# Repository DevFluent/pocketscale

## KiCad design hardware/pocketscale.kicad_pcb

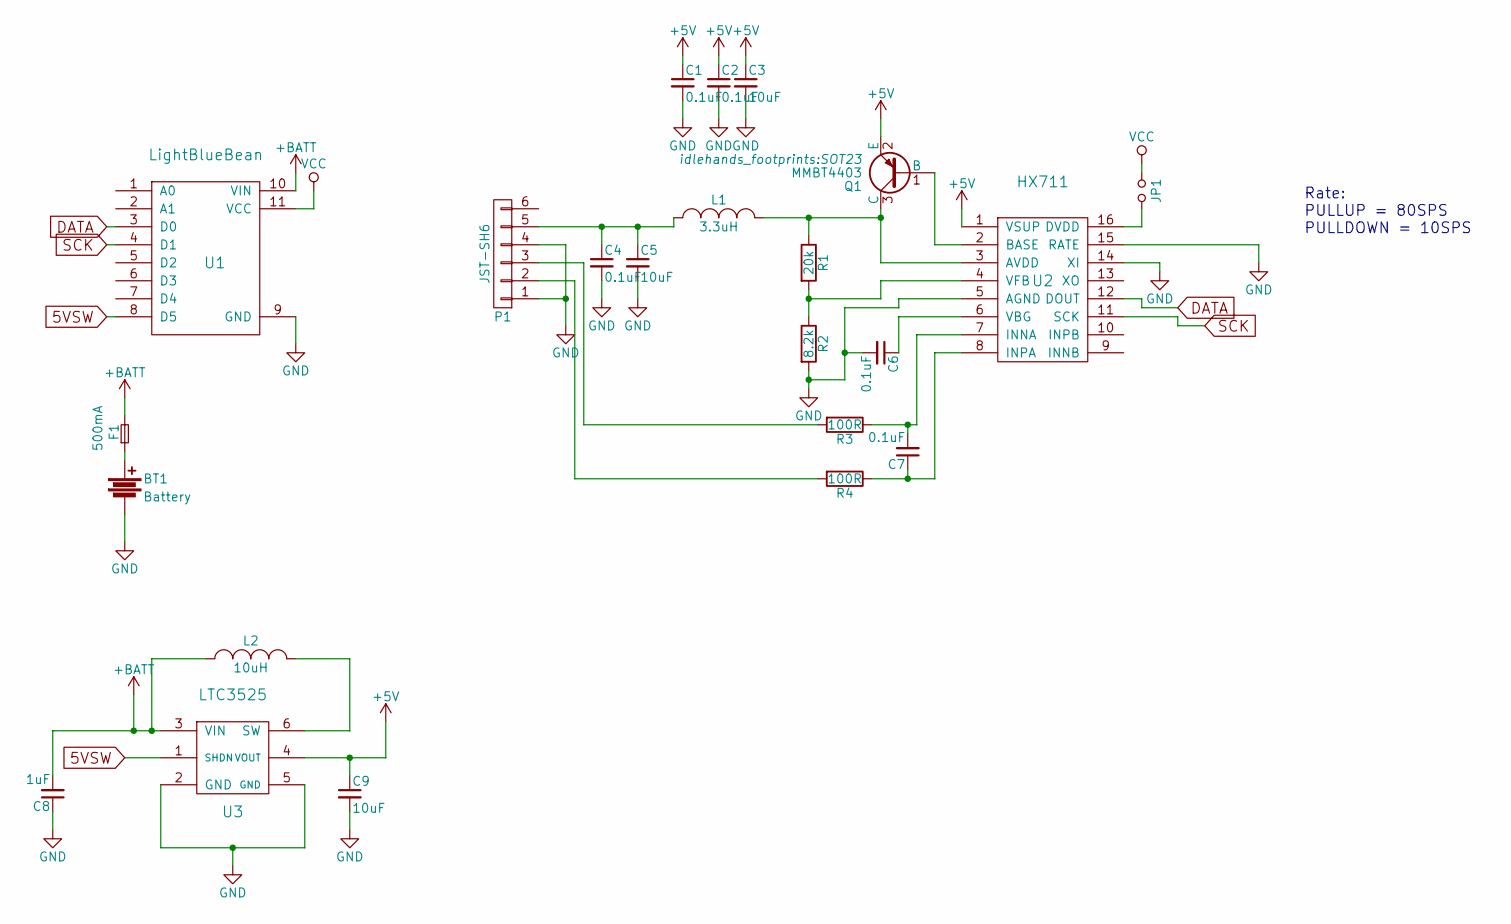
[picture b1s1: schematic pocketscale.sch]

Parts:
BT1: Battery; Pin_Header_Angled_1x02
C1, C2, C4, C6, C7: 0.1uF; C_0402_Hand; Digikey Part No. 490-6328-1-ND
C3, C5, C9: 10uF; c_1206; Digikey Part No. 399-1249-1-ND
C8: 1uF; C_0402_Hand; Digikey Part No. 587-1231-1-ND
F1: 500mA; c_1206
JP1: HX_PWR; Pin_Header_Straight_1x02
L1: 3.3uH; C_SM0603; Digikey Part No. 587-1584-6-ND
L2: 10uH; Inductor_1212; Digikey Part No. 490-6617-1-ND
P1: JST-SH6; Connectors_JST_SM06B-SRSS-TB; Digikey Part No. 455-1806-1-ND
Q1: MMBT4403; SOT23; Digikey Part No. MMBT4403LT3GOSCT-ND
R1: 20k; R_0402_Hand; Digikey Part No. 311-20KJRCT-ND
R2: 8.2k; R_0402_Hand; Digikey Part No. 311-8.2KJRCT-ND
R3, R4: 100R; R_0402_Hand; Digikey Part No. 311-100LRCT-ND
U1: LightBlueBean
U2: HX711; SOP16L
U3: LTC3525; SC70-6; Digikey Part No. LTC3525ESC6-5#TRMPBFCT-ND

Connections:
5VSW: U1.8 (D5), U3.1 (SHDN)
+5V: C1.1, C2.1, C3.1, C9.1, Q1.2 (E), U2.1 (VSUP), U3.4 (VOUT)
+BATT: C8.2, F1.2, L2.1, U1.10 (VIN), U3.3 (VIN)
DATA: U1.3 (D0), U2.12 (DOUT)
GND: BT1.2, C1.2, C2.2, C3.2, C4.2, C5.2, C6.2, C8.1, C9.2, P1.1, P1.4, R2.2, U1.9 (GND), U2.5 (AGND), U2.14 (XI), U2.15 (RATE), U3.2 (GND), U3.5 (GND)
unnamed: BT1.1, F1.1
unnamed: C4.1, C5.1, L1.1, P1.5
unnamed: C6.1, U2.6 (VBG)
unnamed: C7.1, R4.1, U2.8 (INPA)
unnamed: C7.2, R3.1, U2.7 (INNA)
unnamed: JP1.2, U2.16 (DVDD)
unnamed: L1.2, Q1.3 (C), R1.1, U2.3 (AVDD)
unnamed: L2.2, U3.6 (SW)
unnamed: P1.2, R4.2
unnamed: P1.3, R3.2
unnamed: Q1.1 (B), U2.2 (BASE)
unnamed: R1.2, R2.1, U2.4 (VFB)
SCK: U1.4 (D1), U2.11 (SCK)
VCC: JP1.1, U1.11 (VCC)

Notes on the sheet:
Rate: PULLUP = 80SPS PULLDOWN = 10SPS

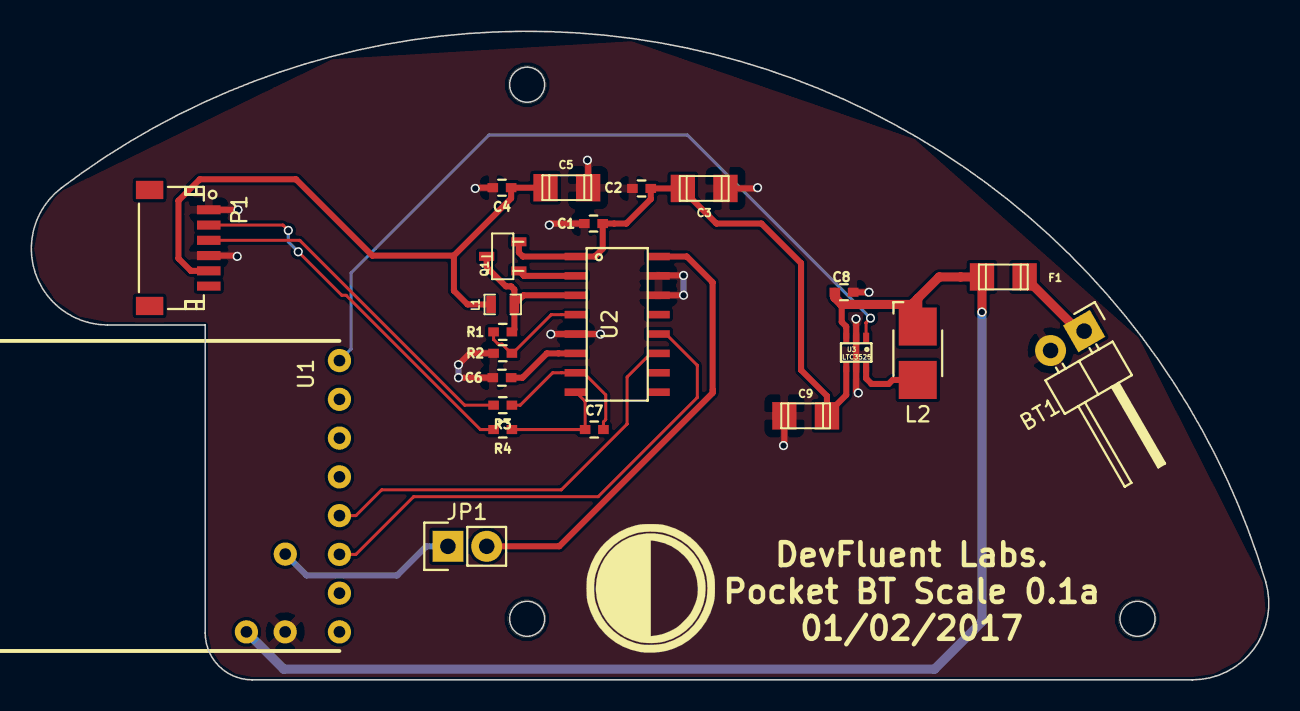
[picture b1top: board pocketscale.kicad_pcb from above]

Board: 2 copper layers, 81.1 x 42.5 mm, 23 parts (0 on the bottom side), 19 nets.
